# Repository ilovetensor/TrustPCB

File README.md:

<div align="center">

# TrustPCB

**Catch board problems before you pay to build them.**

An open-source AI reviewer for KiCad boards that runs real checks and simulations and shows the evidence for every claim.

[Website](https://trustpcb.planary.xyz) · [Releases](https://github.com/ilovetensor/TrustPCB/releases) · [Changelog](CHANGELOG.md) · [Contributing](CONTRIBUTING.md)

 &nbsp;Built on **Meta Muse Spark**. The demo below runs on Muse Spark Open.

<sub>4x speed. [Full video at normal speed](https://trustpcb.vercel.app/#demo).</sub>

*Demo (1 min 42 s): a full review of `samples/nrf52840-node-v3` running on `meta-models/muse-spark-open-1026` via Baseten.*

</div>

## What it is

You upload a KiCad project and say what the board has to do. TrustPCB then:

1. **Measures.** Plain code runs first, with no AI: KiCad's design and electrical rule checks, plus layout analyzers covering decoupling, return paths, the antenna keep-out, RF paths, pair skew, track impedance and more.
2. **Investigates.** Muse studies the board like a senior engineer. It looks at rendered images, ranks suspects, and tests them one at a time with simulations (openEMS for printed antennas, plus power, heat and signal). Suspects are confirmed or ruled out with evidence.
3. **Reports.** You get findings pinned to places on the board, each tied to the tool output behind it, and ranked actions to apply in your own tool.

Upload a new version later and TrustPCB rechecks it and shows what changed.

**TrustPCB never edits a design.** It reads a copy of your files and never writes KiCad or manufacturing files.

## Honest labels

Every result carries one of four labels:

| Label | Meaning |
|---|---|
| **Measured** | KiCad or a layout analyzer measured it on your board geometry |
| **Simulated** | A solver run produced it and passed the trust checks (energy decay, passivity, mesh density, port setup) |
| **Engineering opinion** | Muse's judgment with no measurement behind it. It can never be rated critical |
| **Not tested** | It wasn't checked, and the reason is given |

Muse provides judgment, and tools provide the numbers. The server checks every number with a unit in a finding against tool evidence and rejects any it can't match. If a what-if can't be built on the board, for example lengthening an antenna into the board edge, it fails its trust check and no curve is drawn. Assumptions such as a default stackup are listed in the report.

## Quick start

You need Node.js 22+ and git. [KiCad](https://www.kicad.org/) 10 adds the rule checks, and Docker adds RF simulation. The installer adds [uv](https://docs.astral.sh/uv/) if you don't have it.

**macOS / Linux**

```sh
curl -fsSL https://raw.githubusercontent.com/ilovetensor/TrustPCB/main/install.sh | sh
```

**Windows (PowerShell)**

```powershell
irm https://raw.githubusercontent.com/ilovetensor/TrustPCB/main/install.ps1 | iex
```

The installer clones the repo into `~/trustpcb` (set `TRUSTPCB_DIR` to choose another folder) and installs the dependencies. Then start TrustPCB:

```sh
cd ~/trustpcb && npm run dev                                 # app on http://127.0.0.1:3118
docker build -f docker/ems/Dockerfile -t trustpcb-ems:dev .  # optional: openEMS solver image for RF, takes a while
```

Windows support is new and less tested than macOS and Linux. Please report problems.

Manual install: `git clone https://github.com/ilovetensor/TrustPCB.git && cd trustpcb && npm run setup && npm run dev`.

Then open **Settings**, add a model key (see below), and upload a board. A sample to start with is `samples/nrf52840-node-v3`: zip the folder or drag it in.

Without Docker, everything except RF simulation still works, and RF shows as **Not tested**.

## Model keys: Meta or Baseten

The review agent is Meta's **Muse Spark**. It's a direct tool loop over the Messages API (`server/trustpcb/runners/muse.py`) and can use only the TrustPCB tools. It can't read files, run commands or browse. Set **one** key, either in **Settings** in the app or in `.env`:

| Key | Sent to | Model |
|---|---|---|
| `META_API_KEY` | `https://api.meta.ai` | `muse-spark-1.3` |
| `BASETEN_API_KEY` | `https://inference.baseten.co` | `meta-models/muse-spark-open-1026` (Muse Spark Open) |

- If both are set, Meta is used.
- Each key is sent only to its own host over https, and the runner refuses any other host.
- Keys saved in Settings are stored in a 0600 file in the data folder and never shown again.
- `-contributor` models are refused, because they may use your content for training.
- Reasoning effort is `medium` by default. Set it with `TRUSTPCB_MUSE_EFFORT` (`low`, `medium`, `high` or `xhigh`).

If no key is set, the upload screen says so, and the app uses the deterministic **scripted** runner. That runner calls no model, so it's useful for trying the interface and for tests, but it doesn't review your board.

Check a key before running a real review:

```sh
uv run --project server python scripts/muse-smoke.py   # one text call and one tool round trip
```

**Your board data goes to the model provider.** In a review, board images, part and net data and text from your files are sent to Meta or Baseten. Don't upload a board you aren't allowed to share.

## What each kind of board gets

| Board | What TrustPCB does |
|---|---|
| Printed antenna | Everything, plus an openEMS simulation: S11 across the band, Smith chart, radiation pattern, field and surface current, what-if changes and matching parts |
| Chip antenna or module | A keep-clear review of its clearance zone. RF is reported as **Not tested** |
| No radio | Rule and layout review, plus power, heat and signal simulations where they apply |

A Standard review of a new board takes about 25 to 60 minutes, depending on the model and how many simulations it runs. It takes less when earlier simulations can be reused.

## Limits

- **Simulated, not measured.** Results are predictions from a model of your board. Treat an antenna as unverified until you've measured it on a real board.
- **Antenna frequency** is good to about ±5 % when the stackup is known, and 10 to 15 % or worse when it's assumed. S11 depth and input resistance are less reliable than frequency. Use runs to compare changes, not as absolute claims.
- **Default stackup.** If the board file has no stackup, TrustPCB assumes FR-4 (εr 4.5, tan δ 0.02, 35 µm copper) and says so.
- **KiCad only**, and printed antennas only for RF simulation.
- **Local use only.** The backend binds to loopback with a per-launch token. It has no accounts, so don't expose it to the internet.

## Hackathon

Built for the **Meta Global AI Developer Hackathon** (Indie track, 27 October to 4 November 2026).

- **Meta model:** Muse Spark is the investigating agent in every real review. It uses tool calling, multimodal input (board renders and simulation plots), adaptive thinking and streaming. The demo review ran on Muse Spark Open (`meta-models/muse-spark-open-1026`) via Baseten. The runner works the same way with a Meta API key.
- **Built during the event:** every commit is dated 31 October 2026 or later (`git log --reverse`). Some backend and web scaffolding (launcher, session lock, event stream, token checks) was reused from the author's own earlier code, written in the same period.
- **No other model provider** is used in the product.

## Configuration

Nothing is required: add your model key under **Settings** and you're set. Optional settings, such as reasoning effort, the data folder, DigiKey and Mouser keys and the KiCad path, are listed with comments in [`.env.example`](.env.example).

## Repository layout

```text
server/trustpcb/   backend: api, intake, pcb, analyzers, rf, review, runners
worker/            solver script that runs inside the openEMS container
docker/ems/        pinned openEMS image
web/               Next.js app: 2D board, 3D scene, RF and simulation labs, report
samples/           sample boards
scripts/           launcher, setup, Muse smoke test, demo seeding, tests, release
```

## Contributing

Bug reports, new analyzers and sample boards are welcome. See [CONTRIBUTING.md](CONTRIBUTING.md) for setup, the test commands and how to add an analyzer.

- **Bugs:** open an issue with the board zip (if you can share it) and the review ID.
- **Security:** report privately, as described in [SECURITY.md](SECURITY.md).
- **Conduct:** [Code of Conduct](CODE_OF_CONDUCT.md).

## Releases

Merging a pull request to `main` creates a release automatically:
- label `major` bumps X
- label `minor` bumps Y
- anything else bumps Z

The version fields and [CHANGELOG.md](CHANGELOG.md) are updated, the commit is tagged, and a GitHub Release is published with that version's notes. See [docs/RELEASING.md](docs/RELEASING.md).

## License

[MIT](LICENSE).

KiCad (GPL-3.0-or-later) and openEMS (GPL-3.0) run only as separate programs and aren't linked or redistributed. Sample boards use KiCad library parts under CC BY-SA 4.0 with the KiCad libraries exception ([samples/README.md](samples/README.md)). Other licences are listed in [NOTICE](NOTICE).

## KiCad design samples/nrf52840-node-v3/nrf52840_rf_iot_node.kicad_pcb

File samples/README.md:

# Sample boards

These boards were designed by the TrustPCB author. The board designs (outline, copper, placement and schematic) are released under the repository's MIT licence for testing and demonstration. The KiCad library footprints, symbols and 3D model references inside them are not: see the licence note below.

| Folder | Board |
|---|---|
| `nrf52840-node` | USB-powered nRF52840 sensor node with a printed meander antenna |
| `nrf52840-node-v2` | The same board after the engineer's hand edits for the free re-tune the review confirmed: L1 becomes a 0.51 pF series capacitor, and C20 and C19 are fitted with 0.3 pF and 0.36 pF. Copper and geometry are unchanged, for version rechecks |
| `nrf52840-node-v3` | A revised nRF52840 node, reviewed in the demo video on Muse Spark Open |
| `patch-2g5` | 2.5 GHz patch antenna on FR-4 |
| `usb-ldo-led` | A 40 x 30 mm USB-C powered 3.3 V regulator board (AP2112K, fuse, CC resistors, status LED, test points) with no radio, for the no-wireless review path |

Symbols, footprints and 3D model references that come from the KiCad libraries (the `.pretty` footprint folders, the `.kicad_sym` symbol files, and the `${KICAD10_3DMODEL_DIR}` model paths in the boards) remain under the KiCad library licence, CC BY-SA 4.0 with the KiCad libraries exception, which does not bind designs that use them. The 3D board model used by the web app's bundled sample (`web/public/fixtures/nrf/`) is built from those same library models and is covered the same way. The first three boards are saved by KiCad 10.

`nrf52840-node-v2` is derived from `nrf52840-node`: only the three edited parts differ, so you can diff the two folders to see the change.

These boards are test material. They are unverified designs and contain real faults, which is why they are useful here. Do not manufacture them as they are.

`usb-ldo-led` has no radio, so a review of it skips the simulation phases. It passes kicad-cli DRC, ERC and the schematic parity check with no violations; its parts, symbols and board were generated by a script, and the board file was then refilled and saved by KiCad 10. It still carries a few small layout faults on purpose, such as input and output capacitors more than 3 mm from the regulator pins and power tracks narrower than their net class asks, so a review has something real to report.

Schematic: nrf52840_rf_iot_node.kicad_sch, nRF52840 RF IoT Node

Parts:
C1: 1uF; C_0603_1608Metric
C2: 10uF; C_1206_3216Metric
C3: 2.2uF; C_0603_1608Metric
C4: 4.7uF; C_1206_3216Metric
C5, C6, C7, C8, C9, C10, C11, C13, C14: 100nF; C_0402_1005Metric
C12: 4.7uF; C_0603_1608Metric
C15, C16: 12pF; C_0402_1005Metric
C17, C18: 100nF; C_0603_1608Metric
C19, C20: DNP 0.5pF; C_0402_1005Metric; not fitted
D1: STATUS; LED_0603_1608Metric
F1: 0.5A PTC; Fuse_1206_3216Metric
J1: USB-C 5V IN; USB_C_Receptacle_HRO_TYPE-C-31-M-12
J2: SWD 10P 1.27mm; PinHeader_2x05_P1.27mm_Vertical
L1: 2.2nH; L_0402_1005Metric
R1, R2: 5.1k; R_0603_1608Metric
R3, R4: 22R; R_0603_1608Metric
R5, R6: 4.7k; R_0603_1608Metric
R7: 330R; R_0603_1608Metric
R8, R9: 10k; R_0603_1608Metric
SW1: USER BTN; SW_Push_1P1T_NO_E-Switch_TL3301NxxxxxG
TP1: VBUS_F; TestPoint_THTPad_D1.5mm_Drill0.7mm
TP2: 3V3; TestPoint_THTPad_D1.5mm_Drill0.7mm
TP3: GND; TestPoint_THTPad_D1.5mm_Drill0.7mm
U1: USBLC6-2SC6; SOT-23-6
U2: AP2112K-3.3; SOT-23-5
U3: nRF52840-QFAA; Nordic_AQFN-73-1EP_7x7mm_P0.5mm
U4: LM75C; VSSOP-8_3x3mm_P0.65mm
Y1: 32MHz 9pF; Crystal_SMD_3225-4Pin_3.2x2.5mm

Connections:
ANT_CHIP: C19.1, L1.1, U3.H23 (ANT)
ANT_FEED: C20.1, L1.2
BUTTON_GPIO: C17.1, R8.2, SW1.1, U3.T2 (TRACEDATA2/P0.11)
CC1: J1.A5 (CC1), R1.1
CC2: J1.B5 (CC2), R2.1
I2C_SCL: R6.2, U3.H2 (P0.27), U4.2 (SCL)
I2C_SDA: R5.2, U3.G1 (P0.26), U4.1 (SDA)
LED_GPIO: R7.1, U3.AD8 (P0.13)
RESET_N: J2.10, U3.AC13 (P0.18/~RESET)
SWDCLK: J2.4, U3.AA24 (SWDCLK)
SWDIO: J2.2, U3.AC24 (SWDIO)
TEMP_ALERT: R9.2, U3.U1 (TRACEDATA1/P0.12), U4.3 (O.S.)
USB_D+_ESD: J1.A6 (D+), J1.B6 (D+), R4.1, U1.3 (I/O2), U1.4 (I/O2)
USB_D+_MCU: R4.2, U3.AD6 (D+)
USB_D-_ESD: J1.A7 (D-), J1.B7 (D-), R3.1, U1.1 (I/O1), U1.6 (I/O1)
USB_D-_MCU: R3.2, U3.AD4 (D-)
VBUS_F: C1.1, C2.1, F1.2, TP1.1, U1.5 (VBUS), U2.1 (VIN), U2.3 (EN), U3.AD2 (VBUS)
VBUS_RAW: F1.1, J1.A4 (VBUS), J1.A9 (VBUS), J1.B4 (VBUS), J1.B9 (VBUS)
XTAL_A: C15.1, U3.B24 (XC1), Y1.1
XTAL_B: C16.1, U3.A23 (XC2), Y1.3

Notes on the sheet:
POWER
RF MATCH + ANTENNA FEED
HFXO CRYSTAL
SWD HEADER
MCU + DECOUPLING
STATUS LED
I2C TEMP SENSOR
USER BUTTON
USB PROTECTED SIDE

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
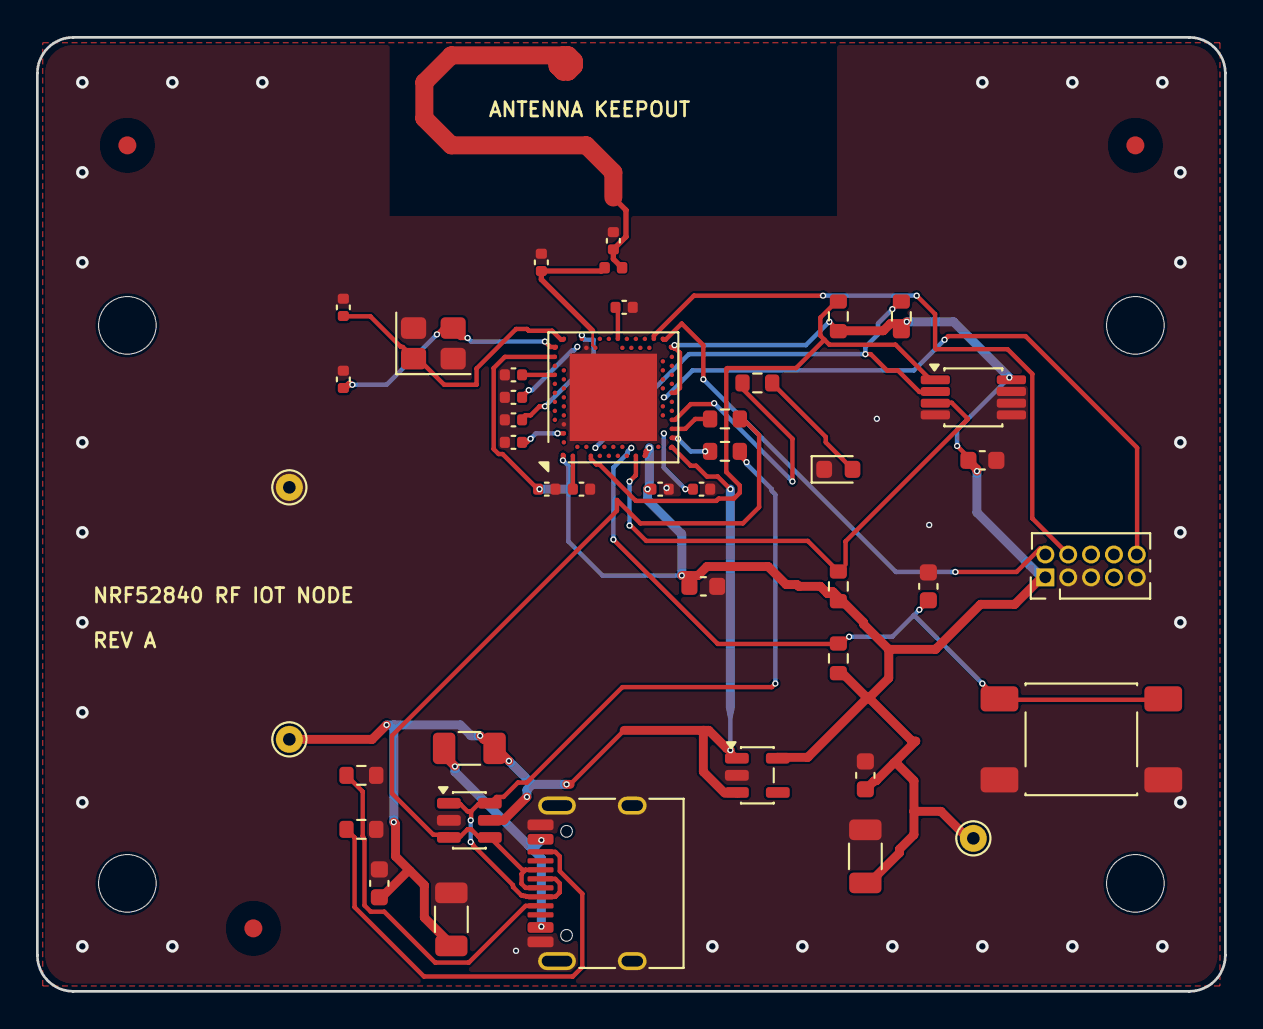
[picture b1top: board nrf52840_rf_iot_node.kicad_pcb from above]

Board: 2 copper layers, 66.0 x 53.0 mm, 50 parts (0 on the bottom side), 30 nets.

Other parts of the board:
FID1, FID2, FID3: GLOBAL FIDUCIAL; Fiducial_1mm_Mask3mm
H1, H2, H3, H4: M3 NPTH; MountingHole_3.2mm_M3

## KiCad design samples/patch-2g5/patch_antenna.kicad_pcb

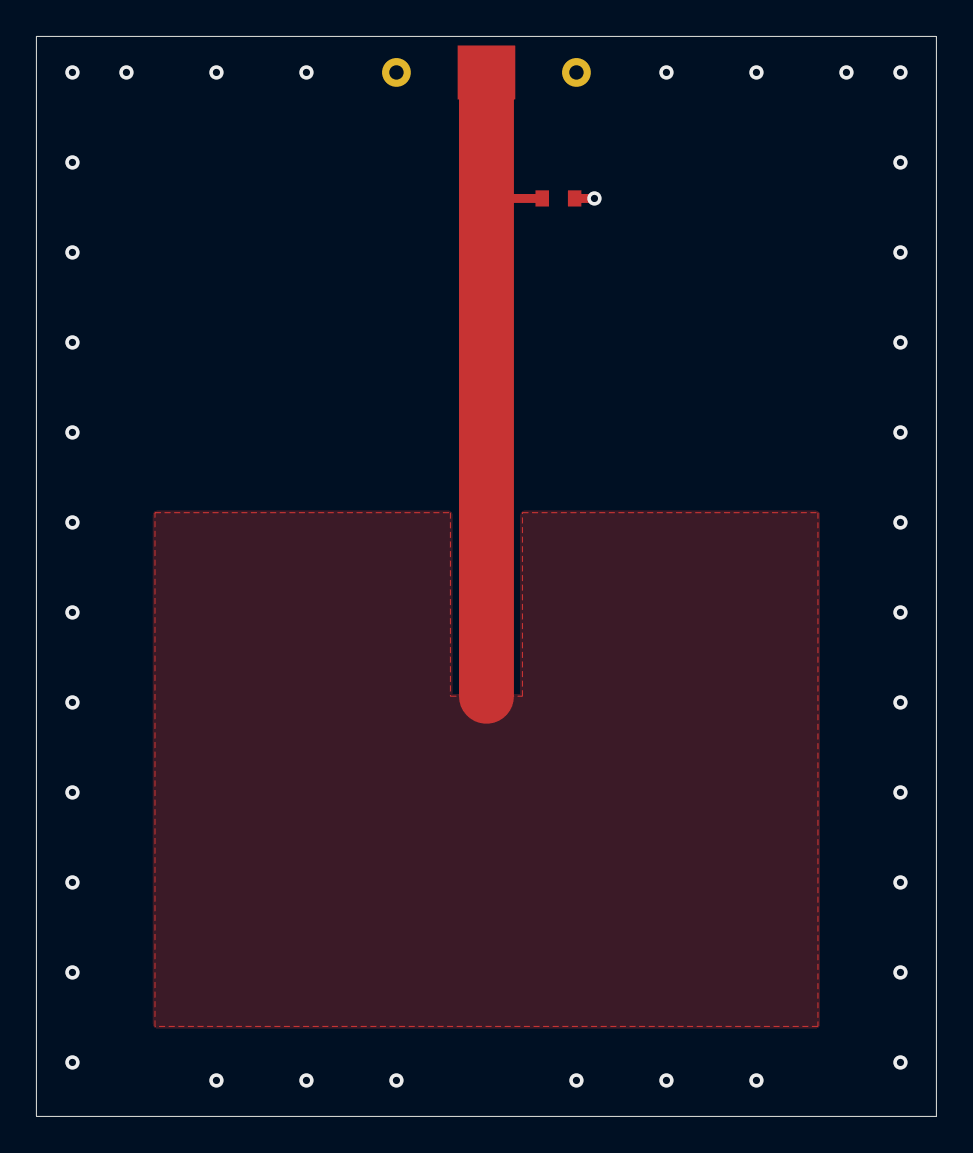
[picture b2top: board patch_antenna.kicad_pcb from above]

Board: 2 copper layers, 50.0 x 60.0 mm, 4 parts (0 on the bottom side), 2 nets.

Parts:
C1, C3: DNP_SERIES; C_0402_1005Metric
C2: DNP_SHUNT; C_0402_1005Metric
J1: SMA_EDGE_2P5G; SMA_Amphenol_132289

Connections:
ANTENNA_50R: C1.1, C1.2, C2.1, C3.1, C3.2, J1.1
GND: C2.2, J1.2

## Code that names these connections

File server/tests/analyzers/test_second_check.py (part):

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    assert len(dec) == 15 and all(c["ic_pin_name"] for c in dec)
    summary = next(c for c in dec if c["pin_class"] == "DEC")["class_summary"]
    assert [x["distance_mm"] for x in summary["capacitors"]] == [5.72, 9.04, 9.05, 9.86, 10.76, 12.92, 16.29]
    assert {x["ic_pin_name"] for x in summary["capacitors"]} == {"DEC1", "DEC2", "DEC3", "DEC4", "DEC5", "DEC6", "DECUSB"}


@needs_ldo
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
